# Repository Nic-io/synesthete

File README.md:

# Synesthete

## Listen to your eyes
A Zephyr RTOS project

This project aims at creating a Eurorack module on the base of Zephyr.

The main functionality is to produce a waveform generated by drawing on
a touch screen.

## Environment 
For a quick start you can use the pre made devcontainer by running
the script here : https://github.com/Nic-io/vittles

## Build

Run ```west build -b nucleo_f446re -- -DSHIELD=adafruit_2_8_tft_touch_v2```

## Hardware
SVG Panel :

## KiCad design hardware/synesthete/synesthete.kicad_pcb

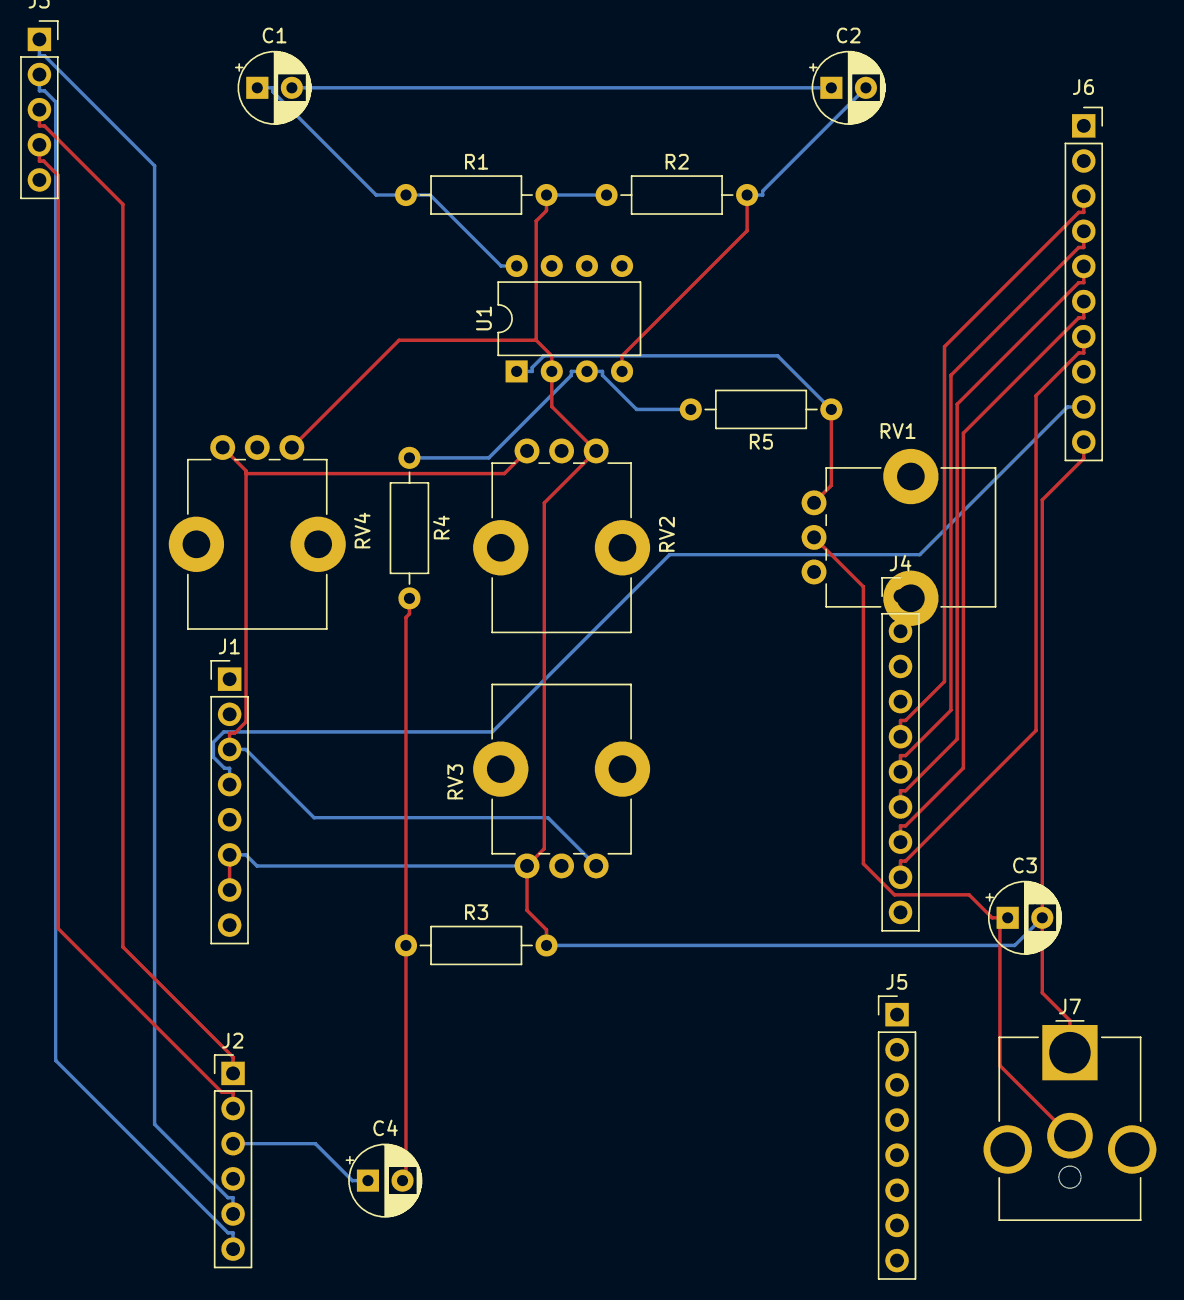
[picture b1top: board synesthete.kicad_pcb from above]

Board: 2 copper layers, 21 parts (0 on the bottom side), 20 nets.

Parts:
C1, C2: 47uF; CP_Radial_D5.0mm_P2.50mm
C3: 1uF; CP_Radial_D5.0mm_P2.50mm
C4: 10uF; CP_Radial_D5.0mm_P2.50mm
J1, J5: Conn_01x08_Male; PinHeader_1x08_P2.54mm_Vertical
J2: Conn_01x06_Male; PinHeader_1x06_P2.54mm_Vertical
J3: Conn_01x05_Female; PinSocket_1x05_P2.54mm_Vertical
J4: Conn_01x10_Male; PinHeader_1x10_P2.54mm_Vertical
J6: Conn_01x10_Female; PinSocket_1x10_P2.54mm_Vertical
J7: Jack-DC; BarrelJack_CUI_PJ-063AH_Horizontal_CircularHoles
R1, R2: 47k; R_Axial_DIN0207_L6.3mm_D2.5mm_P10.16mm_Horizontal
R3: 39k; R_Axial_DIN0207_L6.3mm_D2.5mm_P10.16mm_Horizontal
R4: 3.3k; R_Axial_DIN0207_L6.3mm_D2.5mm_P10.16mm_Horizontal
R5: 10k; R_Axial_DIN0207_L6.3mm_D2.5mm_P10.16mm_Horizontal
RV1: 0-10k; Potentiometer_Alps_RK09K_Single_Vertical
RV2, RV3, RV4: R_POT; Potentiometer_Alps_RK09K_Single_Vertical
U1: LM358; DIP-8_W7.62mm

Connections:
+3V3: J1.3, RV2.1, RV3.1, RV4.1
+5V: J1.4, J6.9
/CLK: J4.9, J6.7
/CS: J4.6, J6.4
/DC: J4.5, J6.3
/Miso: J4.8, J6.6
/Mosi: J4.7, J6.5
/dacout: C4.1, J2.3
/x+: J2.2, J3.4
/x-: J2.6, J3.2
/y+: J2.1, J3.3
/y-: J2.5, J3.1
GND: C3.2, J1.6, J1.7, J6.10, J7.1, R1.2, R2.1, R3.2, RV2.3, RV3.3, RV4.3, U1.2
unnamed: C1.2, C2.1
unnamed: C3.1, J7.2, RV1.2
unnamed: C4.2, R3.1, R4.2
unnamed: R4.1, R5.2, U1.3
unnamed: R5.1, RV1.3, U1.1
VCC: C1.1, R1.1, U1.8
VEE: C2.2, R2.2, U1.4

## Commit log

2021-10-01 first template from display samples
2021-10-12 Basic sample to start with a screen
2021-10-13 Display a 3x3 pixel from memory
2021-10-20 Structurting project, added Threads, preparing ADC for touchScreen
2021-10-26 touch layer added with ADC & GPIOS
2021-10-26 Ignoring doc folder
2021-10-29 Correlate screen positions to wave table values
2021-11-02 Getting DMAs to work with DAC
2021-11-04 adding HAL from ST for timer control
2021-11-04 DMA needed callback to be set
2021-11-05 refactoring, clearer names and structures
2021-11-12 frequency control
2021-11-12 Panel vector file
2021-11-12 Panel vector file with background
2021-11-12 side png for display
2021-11-12 panel had mistakes
2021-12-09 patch upstream DAC driver for stm32 to use DMA
2021-12-15 schematic for shield
2022-02-07 add potentiometers lines to schematics
2022-03-15 adding potentiometers
2022-03-15 Adding clang format config from the kernel
2022-07-06 Clang format
